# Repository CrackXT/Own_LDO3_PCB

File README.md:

# Own_LDO3_PCB
PCB files for external LDO

# Description

This is an external LDO board. The third LDO is for connecting external 3V3 modules (for example sensors) and has a programmable EN control connected to (GP)IO_3 (the designation varies depending on the board and connector used).

The board can be produced here (AISLER) with the files (.brd and .sch) or by any other PCB manufacturer. -> https://aisler.net/

# Spec
Vin:  3,3V<br>
Vout: 3,3V<br>
Iout: 250mA

# Serie

- .dev

# Layout

Top<br>

Bottom<br>

Routing/Dimensions(inch)<br>

Schematic<br>
Schematic as .pdf at the top of the page.

# License

Open hardware, use it, mod it, whatever you want, feel free...

# Thanks!

Own design and layout.

# Version - Build

v1.0 - 07.05.2023

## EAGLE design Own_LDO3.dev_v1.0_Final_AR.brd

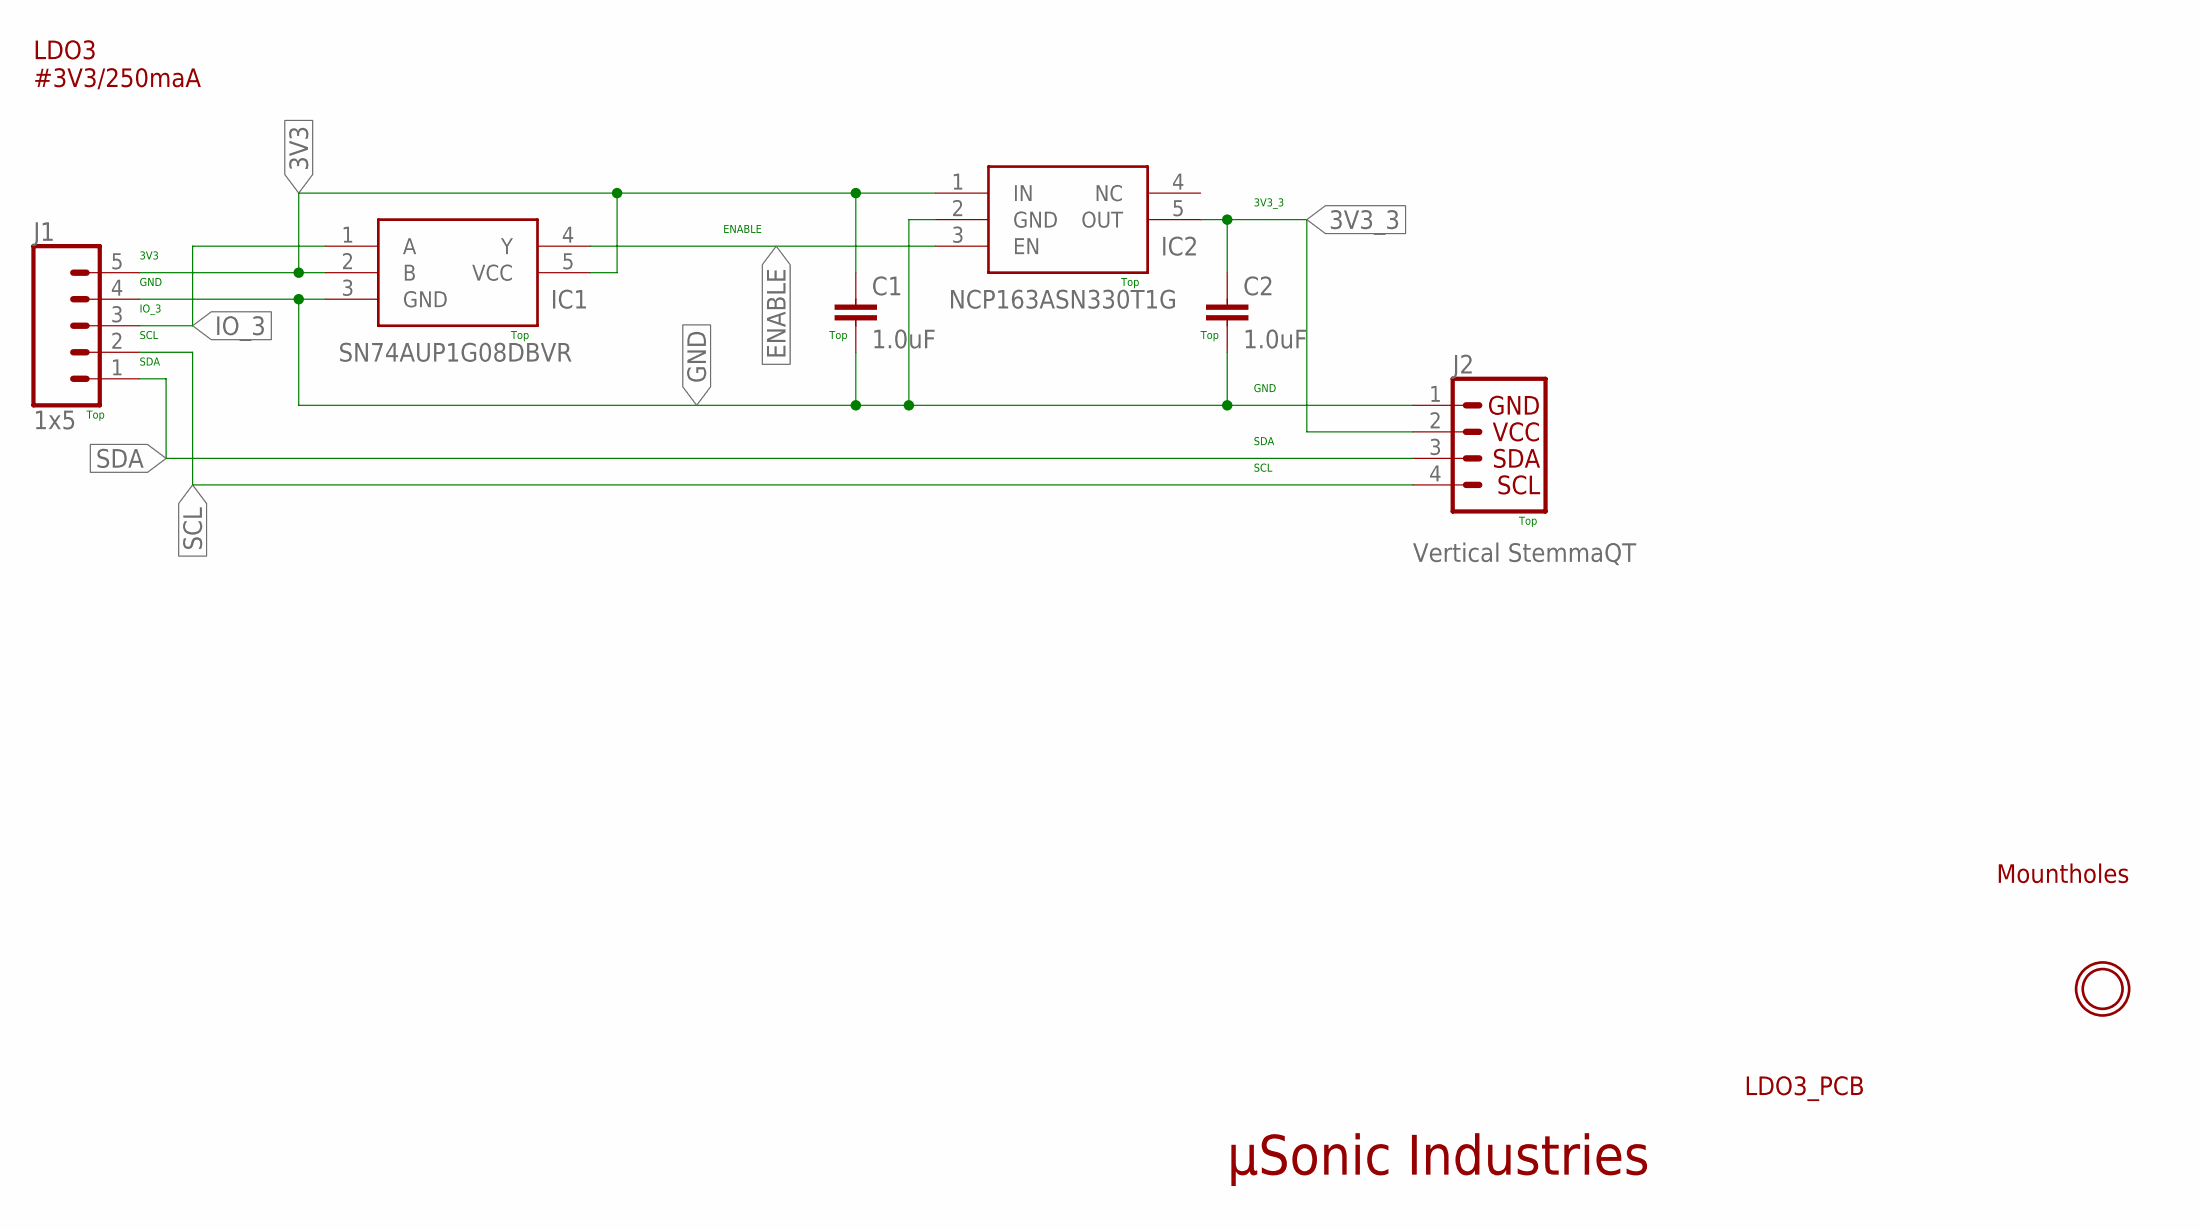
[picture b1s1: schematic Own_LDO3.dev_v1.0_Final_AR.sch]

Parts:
C1, C2: 1.0uF; 0805
IC1: SN74AUP1G08DBVR; SOT95P280X145-5N
IC2: NCP163ASN330T1G; SOT95P280X145-5N
J1: 1x5; 1X05_NO_SILK
J2: Vertical StemmaQT; JST04_1MM_VERT
U$1: MOUNTINGHOLE2.5; MOUNTINGHOLE_2.5_PLATED

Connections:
3V3: C1.1, IC1.2 (B), IC1.5 (VCC), IC2.1 (IN), J1.5
3V3_3: C2.1, IC2.5 (OUT), J2.2
ENABLE: IC1.4 (Y), IC2.3 (EN)
GND: C1.2, C2.2, IC1.3 (GND), IC2.2 (GND), J1.4, J2.1
IO_3: IC1.1 (A), J1.3
SCL: J1.2, J2.4
SDA: J1.1, J2.3

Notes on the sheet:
µSonic Industries
LDO3_PCB
LDO3 #3V3/250maA
Top
Mountholes
ENABLE
3V3_3
GND
SCL
SDA
3V3
IO_3

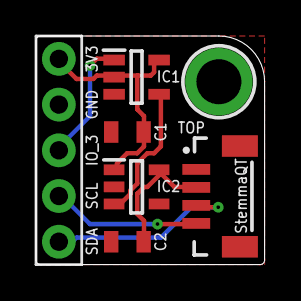
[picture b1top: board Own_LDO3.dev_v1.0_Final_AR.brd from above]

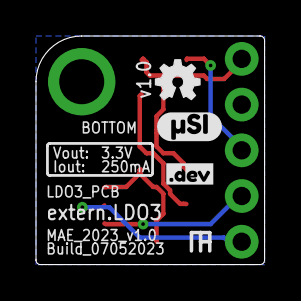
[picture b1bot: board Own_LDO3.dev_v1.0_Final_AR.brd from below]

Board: 2 copper layers, 12.7 x 12.7 mm, 10 parts (3 on the bottom side), 7 nets.

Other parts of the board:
U$2: OSHW-LOGO-MINI
U$3: DEV2
U$4: µSI2

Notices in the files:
parts and their libraries:
microbuilder: This work is placed in the public domain, and may be freely used for commercial and non-commercial work with the following conditions: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
SparkFun-Aesthetics: Licensing: Creative Commons ShareAlike 4.0 International - https://creativecommons.org/licenses/by-sa/4.0
